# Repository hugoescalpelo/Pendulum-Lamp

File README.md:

# Pendulum Lamp

An Iván Abreu Studio Project

This is a project that keeps a pendulum moving

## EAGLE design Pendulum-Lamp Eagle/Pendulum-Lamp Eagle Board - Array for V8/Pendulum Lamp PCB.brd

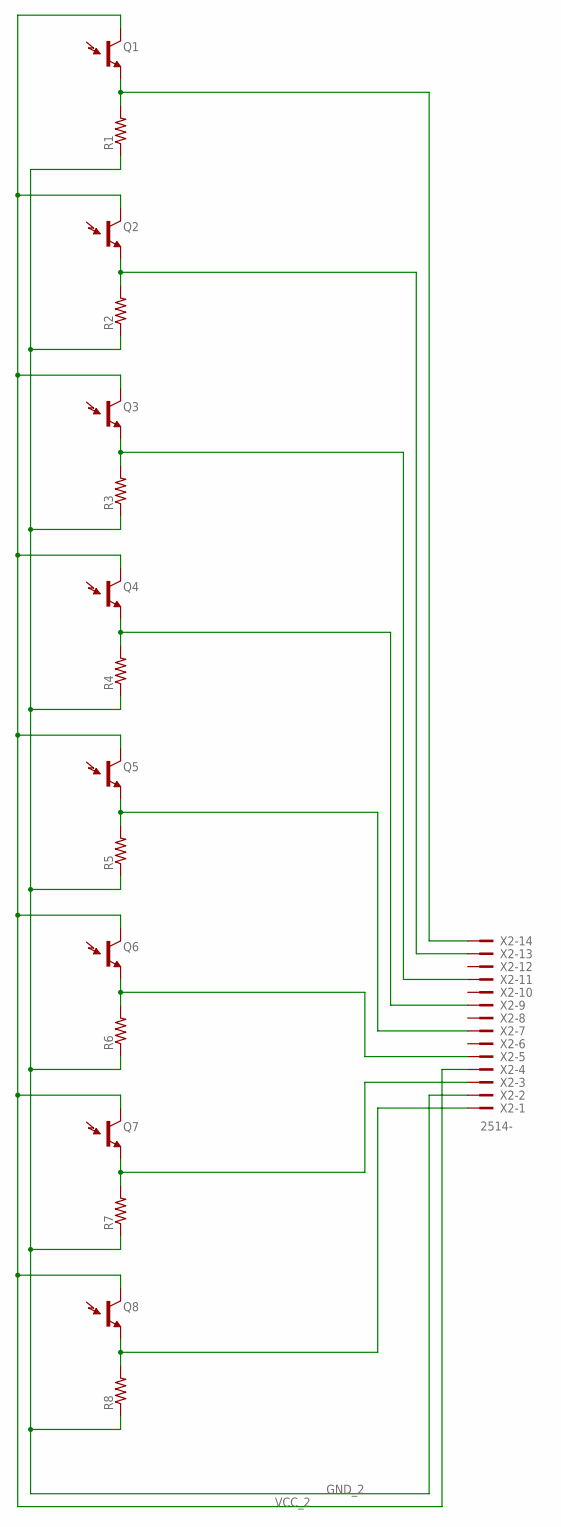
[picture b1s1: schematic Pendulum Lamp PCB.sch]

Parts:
Q1, Q2, Q3, Q4, Q5, Q6, Q7, Q8: LTR-301
R1, R2, R3, R4, R5, R6, R7, R8: R-US_0204/7; 0204/7
X2: 2514-; PAK100/2500-14

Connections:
GND_2: R1.1, R2.1, R3.1, R4.1, R5.1, R6.1, R7.1, R8.1, X2.2
unnamed: Q1.E (E1), R1.2, X2.14
unnamed: Q2.E (E1), R2.2, X2.13
unnamed: Q3.E (E1), R3.2, X2.11
unnamed: Q4.E (E1), R4.2, X2.9
unnamed: Q5.E (E1), R5.2, X2.7
unnamed: Q6.E (E1), R6.2, X2.5
unnamed: Q7.E (E1), R7.2, X2.3
unnamed: Q8.E (E1), R8.2, X2.1
VCC_2: Q1.C (C1), Q2.C (C1), Q3.C (C1), Q4.C (C1), Q5.C (C1), Q6.C (C1), Q7.C (C1), Q8.C (C1), X2.4

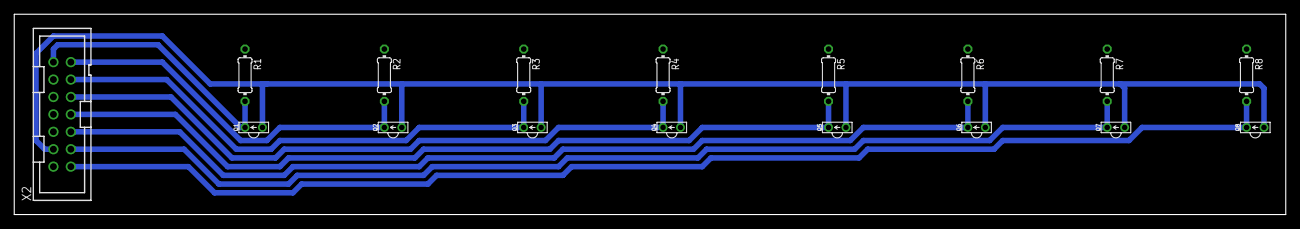
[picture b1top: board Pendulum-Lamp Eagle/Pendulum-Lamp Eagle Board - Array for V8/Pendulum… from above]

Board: 2 copper layers, 185.4 x 29.2 mm, 17 parts (0 on the bottom side), 10 nets.

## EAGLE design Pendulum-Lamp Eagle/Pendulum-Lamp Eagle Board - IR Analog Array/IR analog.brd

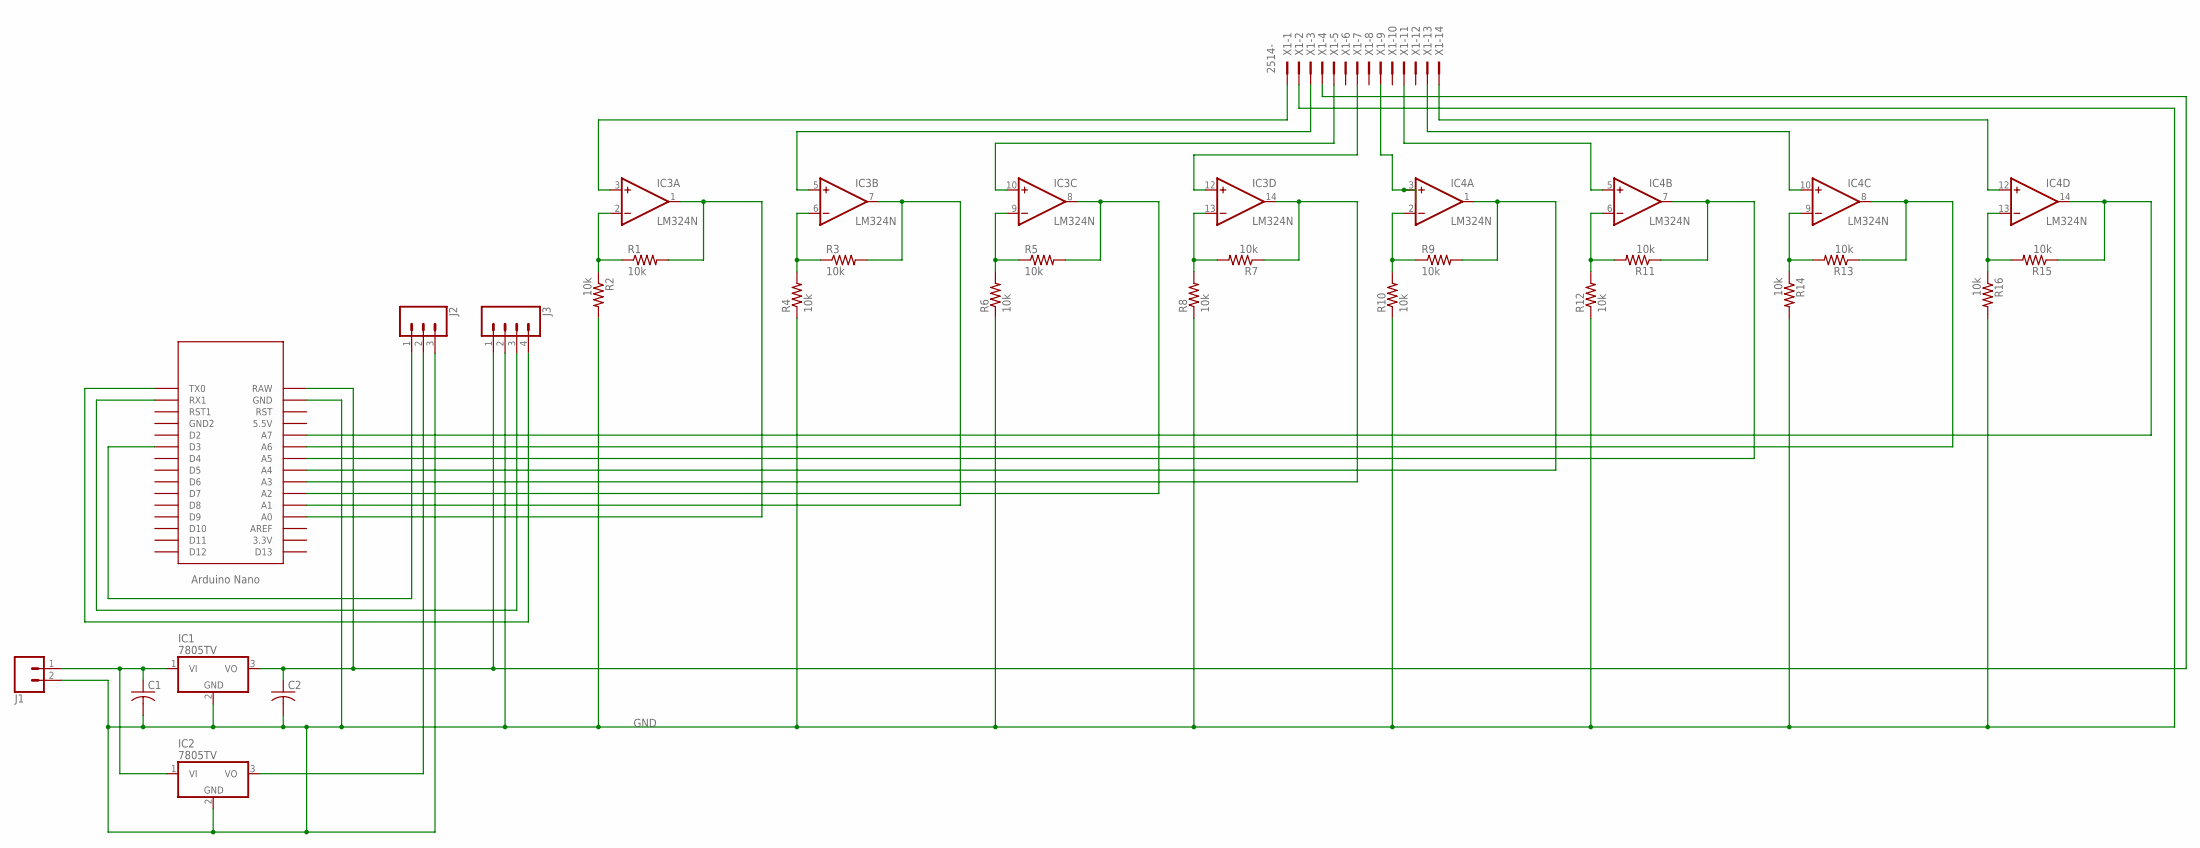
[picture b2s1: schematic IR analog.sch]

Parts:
C1, C2: C-US025-060X050; C025-060X050
IC1, IC2: 7805TV; TO220V
IC3, IC4: LM324N; DIL14
J1: CONN_023.5MM_LOCK; SCREWTERMINAL-3.5MM-2_LOCK
J2: CONN_03LONGPADS; 1X03_LONGPADS
J3: CONN_04LONGPADS; 1X04_LONGPADS
R1, R2, R3, R4, R5, R6, R7, R8, R9, R10, R11, R12, R13, R14, R15, R16: 10k; 0204/5
U$1: NANO
X1: 2514-; PAK100/2500-14

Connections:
GND: C1.2, C2.2, IC1.2 (GND), IC2.2 (GND), IC3.11 (V-), IC4.11 (V-), J1.2, J2.3, J3.2, R2.2, R4.1, R6.1, R8.1, R10.1, R12.1, R14.2, R16.2, U$1.GND, X1.2
unnamed: C1.1, IC1.1 (VI), IC2.1 (VI), J1.1
unnamed: C2.1, IC1.3 (VO), J3.1, U$1.RAW, X1.4
unnamed: IC4.9 (-IN), R13.2, R14.1
unnamed: IC3.2 (-IN), R1.1, R2.1
unnamed: IC3.1 (OUT), R1.2, U$1.A0
unnamed: IC3.7 (OUT), R3.2, U$1.A1
unnamed: IC3.6 (-IN), R3.1, R4.2
unnamed: IC3.8 (OUT), R5.2, U$1.A2
unnamed: IC3.9 (-IN), R5.1, R6.2
unnamed: IC3.13 (-IN), R7.2, R8.2
unnamed: IC3.14 (OUT), R7.1, U$1.A3
unnamed: IC4.1 (OUT), R9.2, U$1.A4
unnamed: IC4.2 (-IN), R9.1, R10.2
unnamed: IC4.6 (-IN), R11.2, R12.2
unnamed: IC4.7 (OUT), R11.1, U$1.A5
unnamed: IC4.8 (OUT), R13.1, U$1.A6
unnamed: IC4.14 (OUT), R15.1, U$1.A7
unnamed: IC4.13 (-IN), R15.2, R16.1
unnamed: IC3.3 (+IN), X1.1
unnamed: IC3.5 (+IN), X1.3
unnamed: IC3.10 (+IN), X1.5
unnamed: IC3.12 (+IN), X1.7
unnamed: IC4.3 (+IN), X1.9
unnamed: IC4.10 (+IN), X1.13
unnamed: IC4.5 (+IN), X1.11
unnamed: IC4.12 (+IN), X1.14
unnamed: J2.1, U$1.D3
unnamed: IC2.3 (VO), J2.2
unnamed: J3.3, U$1.RX1
unnamed: J3.4, U$1.TX0
V+: IC3.4 (V+), IC4.4 (V+)

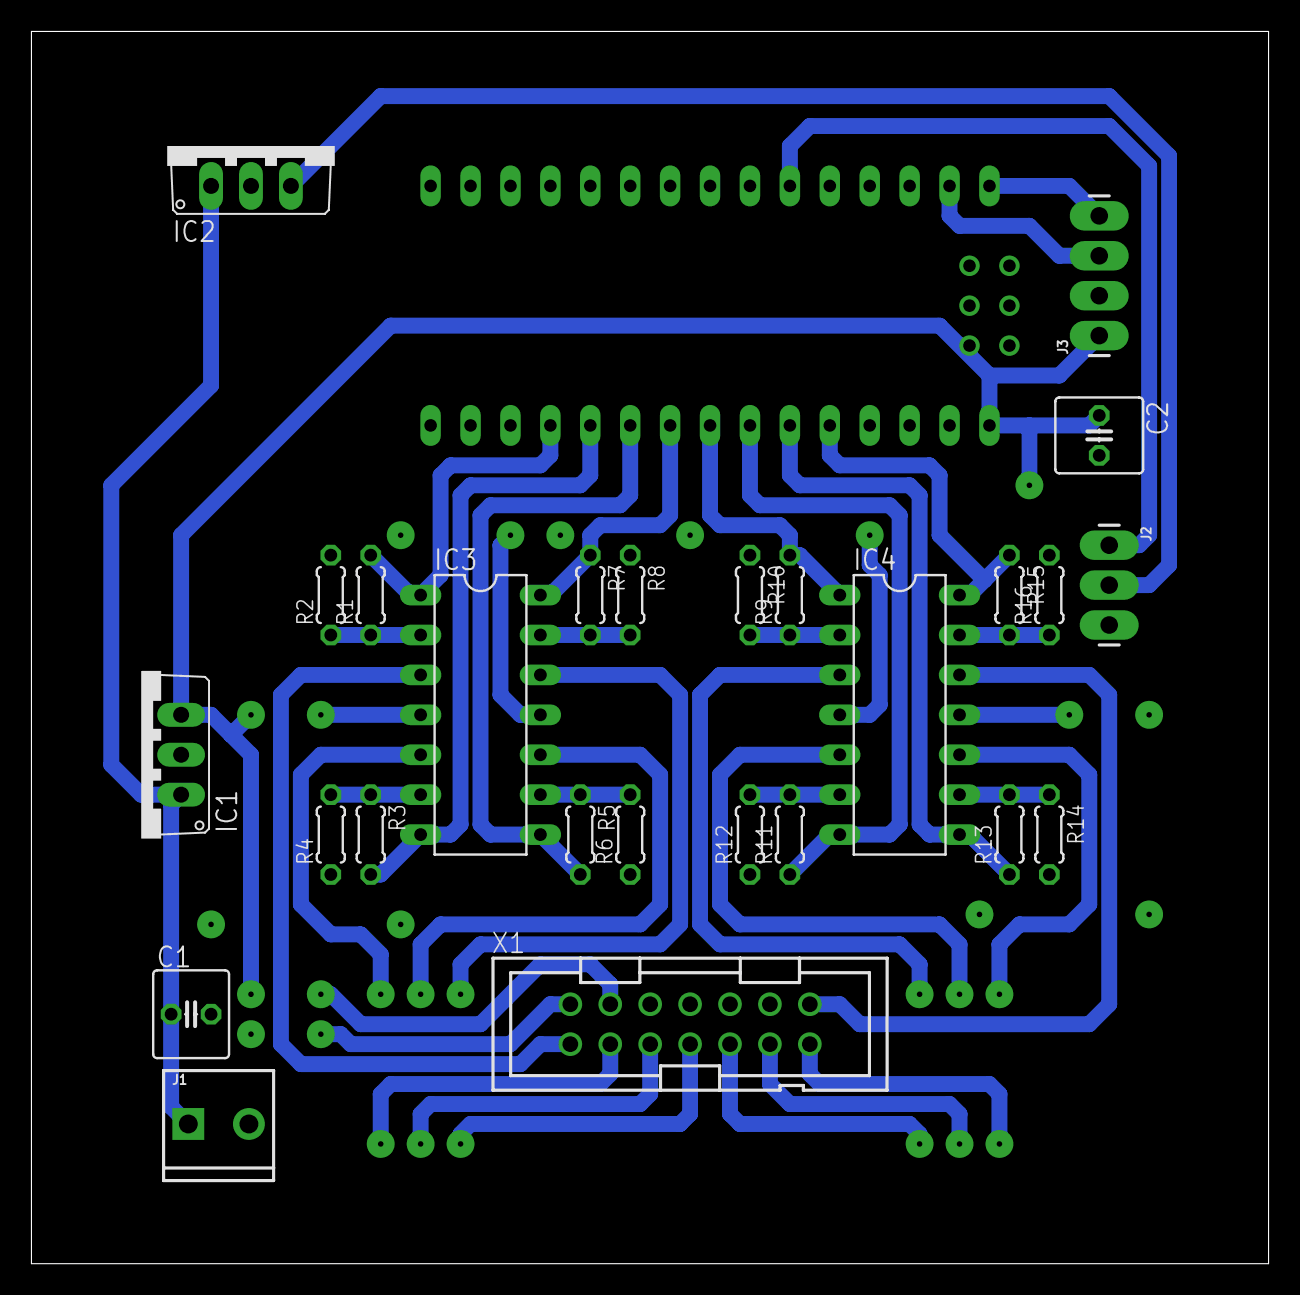
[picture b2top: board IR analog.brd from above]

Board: 2 copper layers, 78.7 x 78.4 mm, 27 parts (0 on the bottom side), 32 nets.

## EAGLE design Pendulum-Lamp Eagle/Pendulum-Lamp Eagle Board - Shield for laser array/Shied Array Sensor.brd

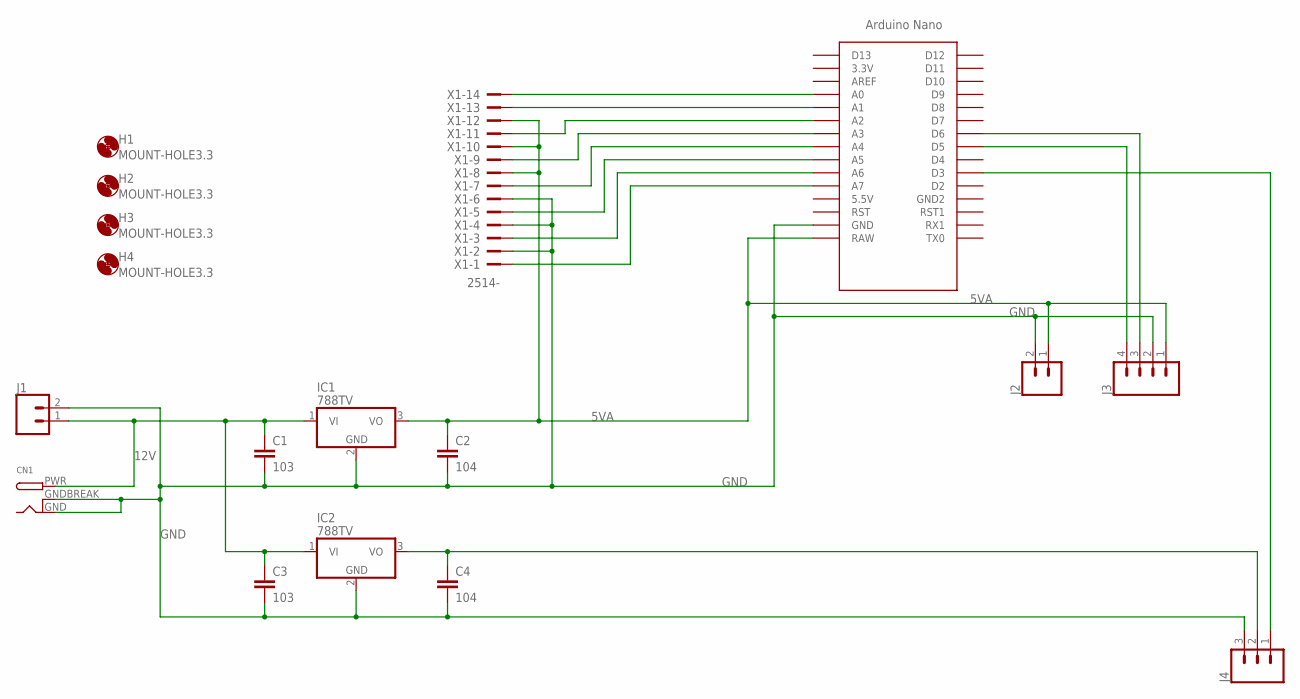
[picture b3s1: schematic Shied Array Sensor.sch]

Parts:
C1, C3: 103; C050-024X044
C2, C4: 104; C050-024X044
CN1: DCBARRELPTH; DCJACK_2MM_PTH
H1, H2, H3, H4: MOUNT-HOLE3.3; 3,3
IC1, IC2: 788TV; TO220V
J1, J2: CONN_023.5MM_LOCK; SCREWTERMINAL-3.5MM-2_LOCK
J3: CONN_04LONGPADS; 1X04_LONGPADS
J4: CONN_03LONGPADS; 1X03_LONGPADS
U$1: NANO
X1: 2514-; PAK100/2500-14

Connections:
5VA: C2.1, IC1.3 (VO), J2.1, J3.1, U$1.RAW, X1.8, X1.10, X1.12
12V: C1.1, C3.1, CN1.PWR, IC1.1 (VI), IC2.1 (VI), J1.1
GND: C1.2, C2.2, C3.2, C4.2, CN1.GND, CN1.GNDBREAK, IC1.2 (GND), IC2.2 (GND), J1.2, J2.2, J3.2, J4.3, U$1.GND, X1.2, X1.4, X1.6
unnamed: U$1.A0, X1.14
unnamed: U$1.A1, X1.13
unnamed: U$1.A2, X1.11
unnamed: U$1.A3, X1.9
unnamed: U$1.A4, X1.7
unnamed: U$1.A5, X1.5
unnamed: U$1.A6, X1.3
unnamed: U$1.A7, X1.1
unnamed: J3.4, U$1.D5
unnamed: C4.1, IC2.3 (VO), J4.2
unnamed: J3.3, U$1.D6
unnamed: J4.1, U$1.D3

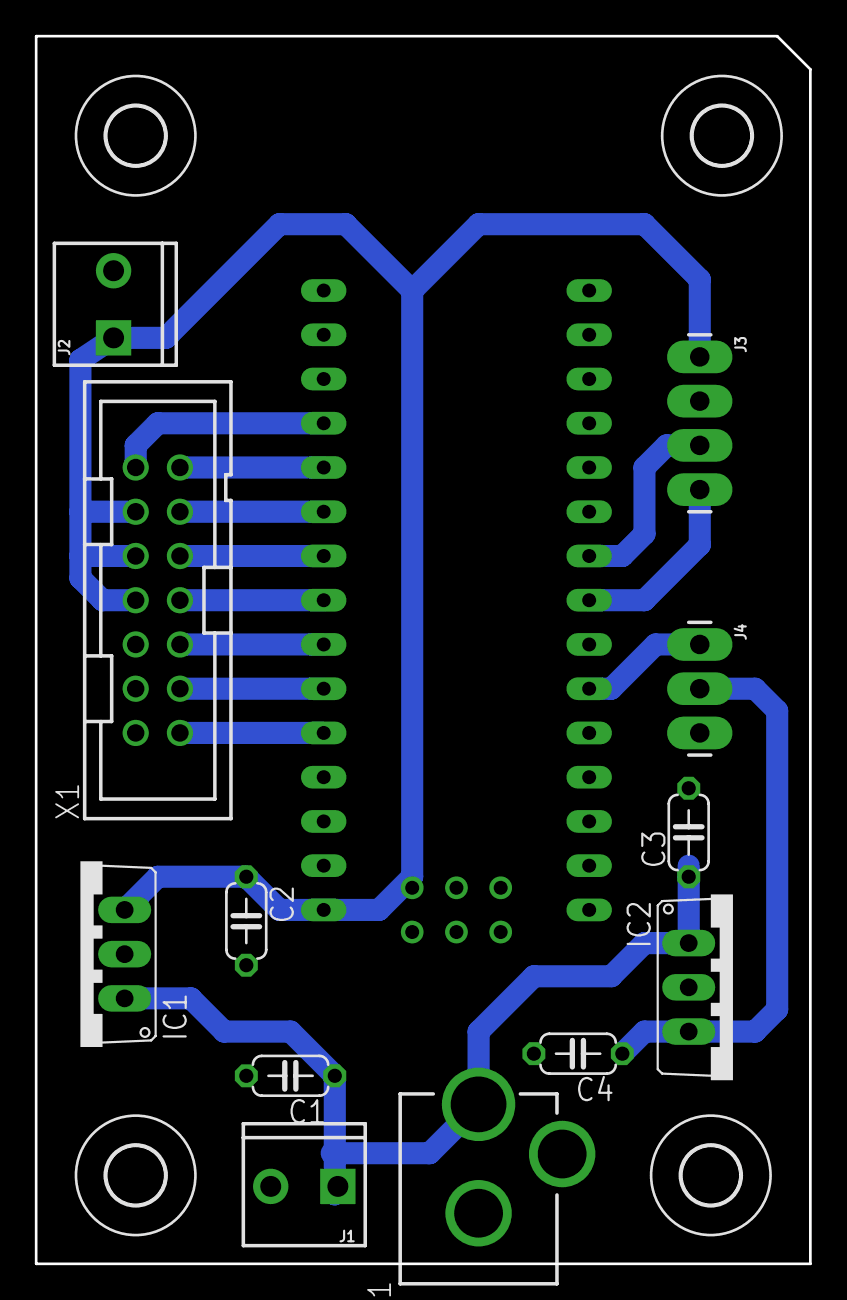
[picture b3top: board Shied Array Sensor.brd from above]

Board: 2 copper layers, 44.4 x 70.5 mm, 17 parts (0 on the bottom side), 15 nets.

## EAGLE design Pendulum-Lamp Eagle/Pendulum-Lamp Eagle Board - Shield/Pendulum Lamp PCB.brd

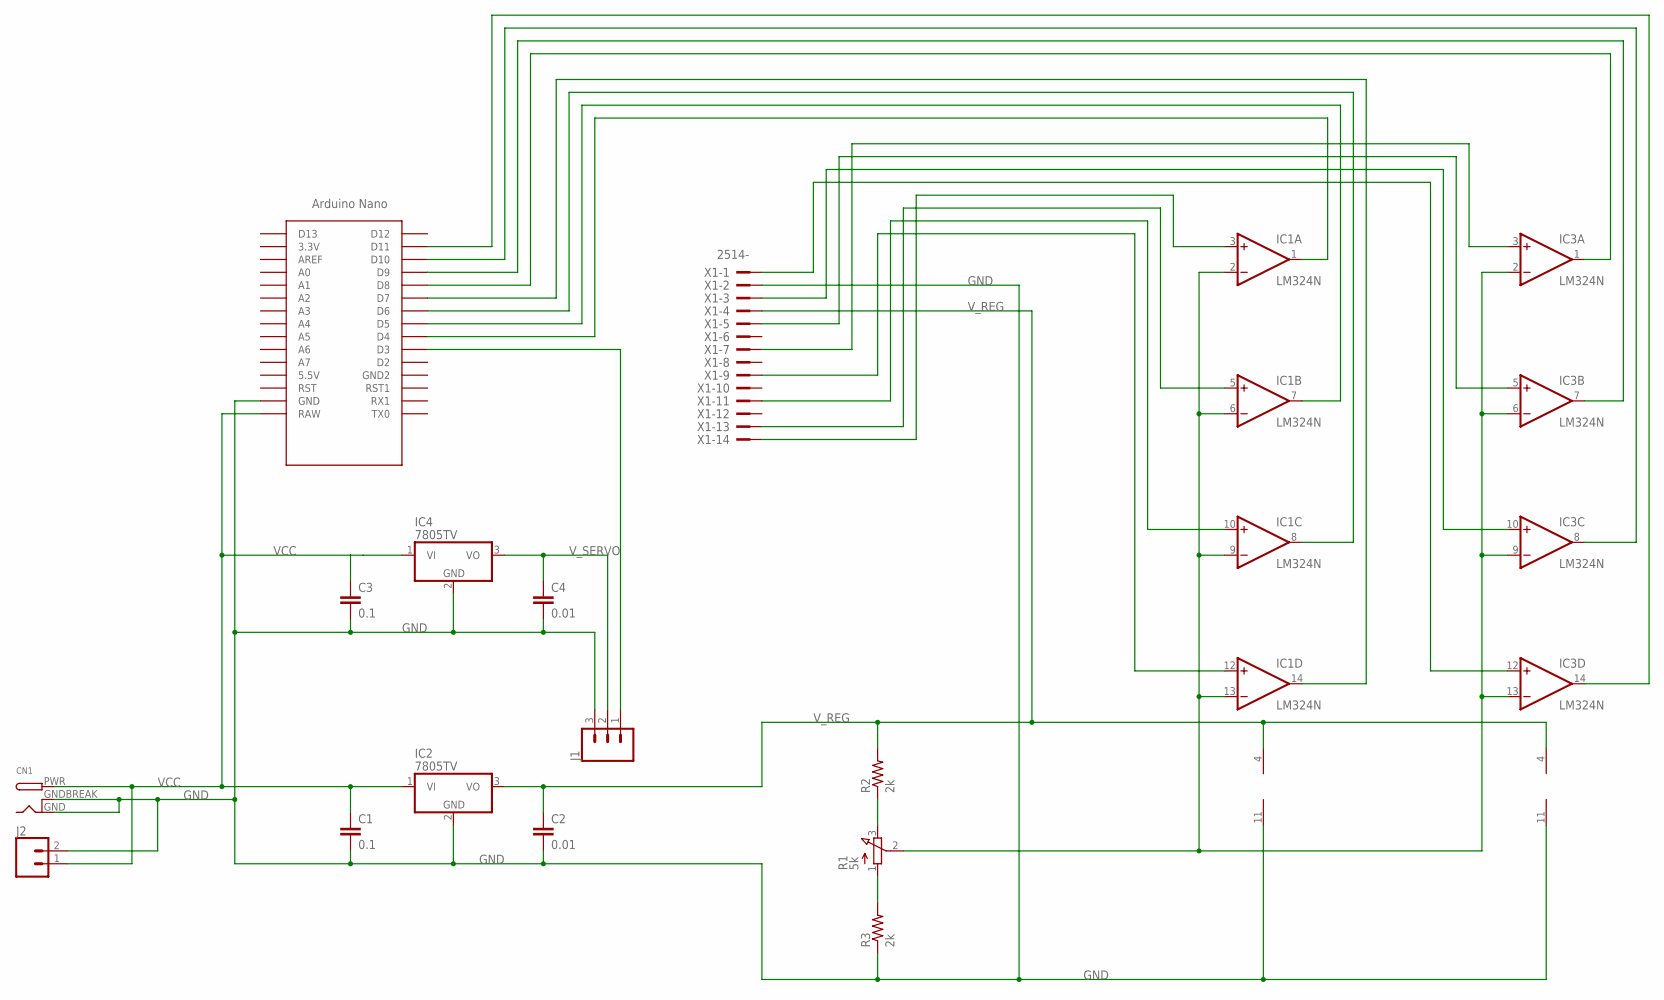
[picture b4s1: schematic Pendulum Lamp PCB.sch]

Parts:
C1, C3: 0.1; C025-030X050
C2, C4: 0.01; C025-030X050
CN1: DCBARRELPTH; DCJACK_2MM_PTH
IC1, IC3: LM324N; DIL14
IC2, IC4: 7805TV; TO220V
J1: CONN_03LONGPADS; 1X03_LONGPADS
J2: CONN_023.5MM_LOCK; SCREWTERMINAL-3.5MM-2_LOCK
R1: 5k; 3RP/1610N
R2, R3: 2k; 0204/7
U$1: NANO
X1: 2514-; PAK100/2500-14

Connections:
GND: C1.2, C2.2, C3.2, C4.2, CN1.GND, CN1.GNDBREAK, IC1.11 (V-), IC2.2 (GND), IC3.11 (V-), IC4.2 (GND), J1.3, J2.2, R3.1, U$1.GND, X1.2
unnamed: IC1.3 (+IN), X1.14
unnamed: IC3.5 (+IN), X1.5
unnamed: J1.1, U$1.D3
unnamed: IC3.10 (+IN), X1.3
unnamed: R1.1 (A), R3.2
unnamed: R1.3 (E), R2.1
unnamed: IC1.2 (-IN), IC1.6 (-IN), IC1.9 (-IN), IC1.13 (-IN), IC3.2 (-IN), IC3.6 (-IN), IC3.9 (-IN), IC3.13 (-IN), R1.2 (S)
unnamed: IC1.1 (OUT), U$1.D4
unnamed: IC1.7 (OUT), U$1.D5
unnamed: IC1.8 (OUT), U$1.D6
unnamed: IC1.14 (OUT), U$1.D7
unnamed: IC3.1 (OUT), U$1.D8
unnamed: IC3.7 (OUT), U$1.D9
unnamed: IC3.8 (OUT), U$1.D10
unnamed: IC3.14 (OUT), U$1.D11
unnamed: IC3.12 (+IN), X1.1
unnamed: IC1.12 (+IN), X1.9
unnamed: IC1.5 (+IN), X1.13
unnamed: IC1.10 (+IN), X1.11
unnamed: IC3.3 (+IN), X1.7
VCC: C1.1, C3.1, CN1.PWR, IC2.1 (VI), IC4.1 (VI), J2.1, U$1.RAW
V_REG: C2.1, IC1.4 (V+), IC2.3 (VO), IC3.4 (V+), R2.2, X1.4
V_SERVO: C4.1, IC4.3 (VO), J1.2

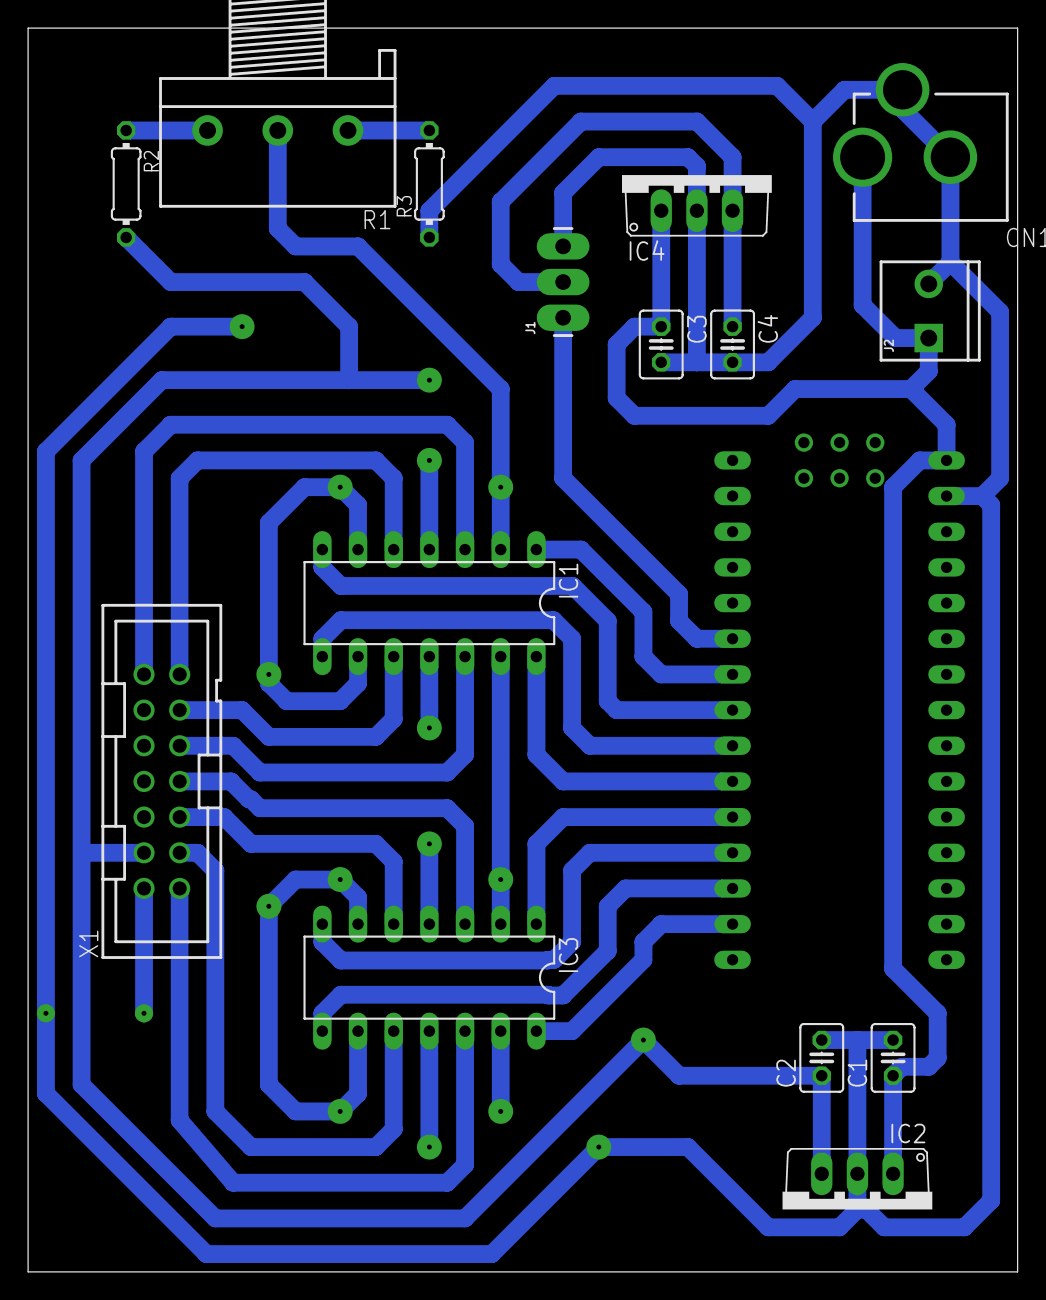
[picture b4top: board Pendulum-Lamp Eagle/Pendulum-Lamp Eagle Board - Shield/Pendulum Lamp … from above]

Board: 2 copper layers, 70.5 x 88.6 mm, 16 parts (0 on the bottom side), 24 nets.

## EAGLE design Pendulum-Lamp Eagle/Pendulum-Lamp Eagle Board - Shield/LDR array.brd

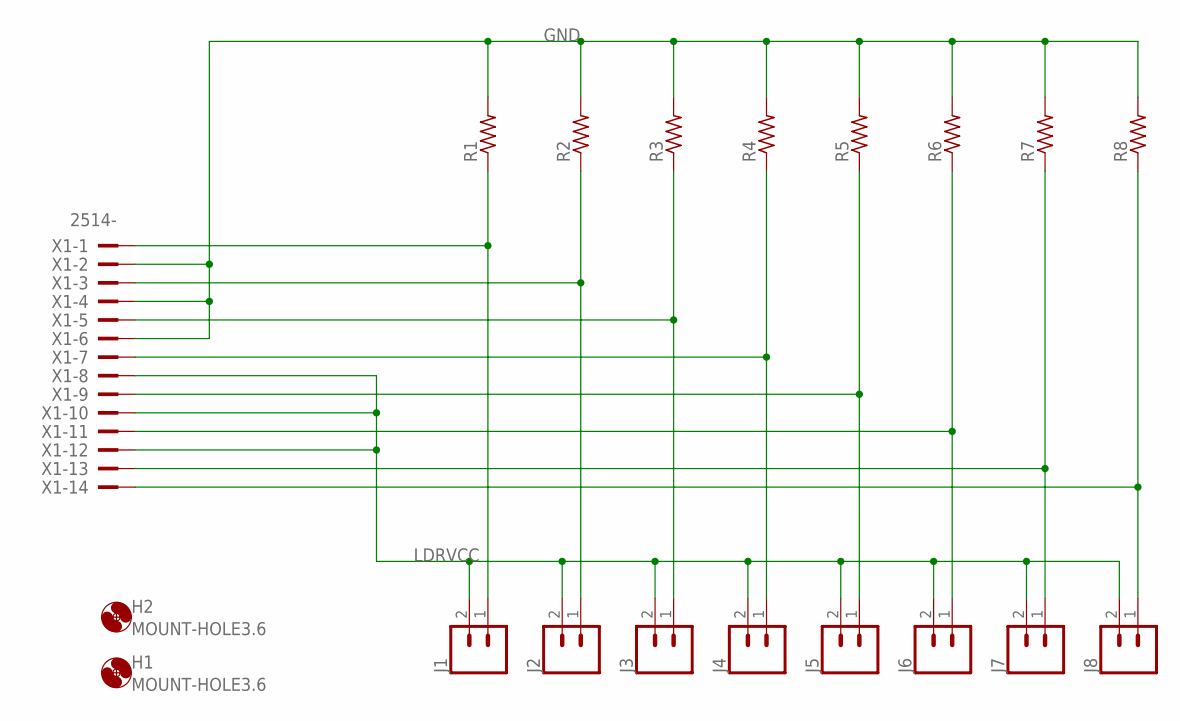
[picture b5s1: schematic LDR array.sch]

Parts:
H1, H2: MOUNT-HOLE3.6; 3,6
J1, J2, J3, J4, J5, J6, J7, J8: CONN_023.5MM_LOCK; SCREWTERMINAL-3.5MM-2_LOCK
R1, R2, R3, R4, R5, R6, R7, R8: R-US_0204/7; 0204/7
X1: 2514-; PAK100/2500-14

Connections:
GND: R1.2, R2.2, R3.2, R4.2, R5.2, R6.2, R7.2, R8.2, X1.2, X1.4, X1.6
LDRVCC: J1.2, J2.2, J3.2, J4.2, J5.2, J6.2, J7.2, J8.2, X1.8, X1.10, X1.12
unnamed: J1.1, R1.1, X1.1
unnamed: J2.1, R2.1, X1.3
unnamed: J3.1, R3.1, X1.5
unnamed: J4.1, R4.1, X1.7
unnamed: J5.1, R5.1, X1.9
unnamed: J6.1, R6.1, X1.11
unnamed: J7.1, R7.1, X1.13
unnamed: J8.1, R8.1, X1.14

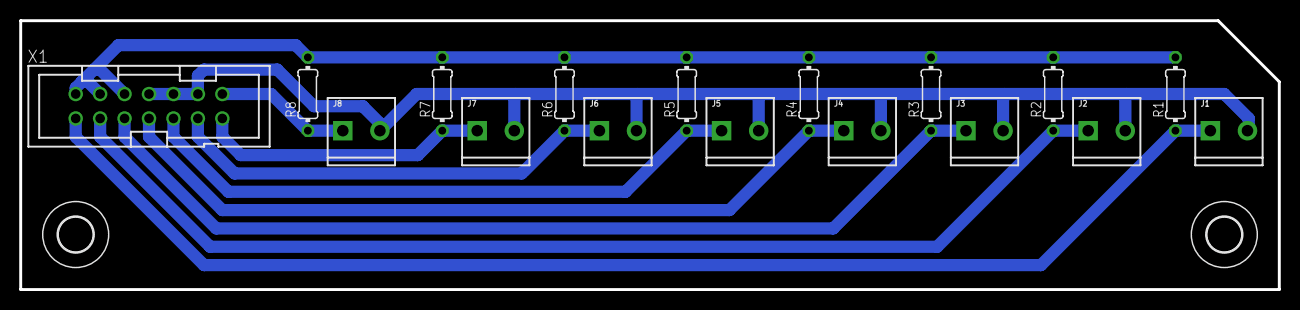
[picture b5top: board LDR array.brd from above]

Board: 2 copper layers, 130.8 x 27.9 mm, 19 parts (0 on the bottom side), 10 nets.

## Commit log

2018-02-13 First files added
2018-02-13 Commentary on Read me file
2018-02-13 Firs commit
    Schematic Added
2018-02-13 Some mechanical references modified
    Re opened assembly files, re adjusts paths to referenced assemby. Made a layout to determine the pcb form factor based on the mechanism. Gosh, maybe I shoud migrate to Fusion 360
2018-02-14 PCB board finished
    Main pcb board finished. Some solid works parts modied
2018-02-14 DXF cam layout added
2018-02-14 CAM DXF file finished
    Added some corrections to schematic supply. DXF file processed.
2018-02-14 Sensor Array finished
    Added sensor array in Eagle and DXF
2018-02-15 CAM Files added
2018-02-19 Test code
    Sensor array test coded completed
2018-02-19 Eagle PCB Project Splitted
2018-02-19 Circuit Holder added
    A 3d printed pieces to make shure the lamp wire stays in IR range
2018-02-20 Circuit Holder splitted
    Circuit holder splitted to 3d printing easyness
2018-02-20 G Code added
2018-02-20 Bitwise operations added
    Arduino code updated with bitwise operations
2018-02-20 First active test working
    A pen has used to obstuct the lamp module and it reacts to the simulating moving of the lamp wire
2018-02-21 Firtst succesful test
    Auto sync achieved. Some minor bugs founded. Stills sync after lose track of the lamps wire position
2018-02-21 Take me out sequence added
    It was needed a take me out sequence because sometimes the lamp get stucked. Also, I need to redesign the way changes are detected
2018-02-21 Updated lecture logics
    The way is read and updated de register info of the sensors reading was corrected. A take me out sequence is not needed anymore, however remains commented.
2018-02-23 Working Code
2018-02-23 Proporcionality at extension and delay time added
2018-02-23 Proportional ignition added
2018-02-24 Test code added
2018-02-24 A little order to the code
    It was a mess
2018-02-27 Laser sensor array started
2018-02-27 Succesful model
    It was needed an alignment in base extensors
2018-02-28 First succesful model
2018-02-28 Circuit adjusted. Laser array sch started
2018-02-28 Laser array and ldr array pcb circuits designed
2018-02-28 Shield pcb first version
2018-02-28 Rhino patter added
2018-03-01 Patern fixed
    Layer ortederd
2018-03-06 New arduino code version
2018-03-06 Working basic laser array fix
2018-03-06 Add promedier function Added
2018-03-06 Primedier trimmer added
2018-03-06 No detect promediator added
2018-03-06 Some order
2018-03-07 New logic code added
2018-03-08 Average sequence added with fixed logics
2018-03-08 Ignition motion detection redesigned
2018-03-09 Servo movement bonded to intensity
2018-03-09 Direction detecto added
2018-03-09 change direction detector with half steps added
2018-03-10 New Logics
2018-03-12 Adjusted to day values
2018-03-12 Adder added
2018-03-12 Dinamic threshold added
2018-03-13 Average sequence added
2018-03-13 lecture feedback
2018-03-13 Self referenced averaged feedback functional version
2018-03-13 Comentary added
2018-03-13 More comentary
2018-03-22 Line laser parts added
2018-05-18 New parts added
2018-06-25 New Design
2018-07-24 Minor changes in arms
    Arms didnt work
2018-07-26 Drawings Added
2018-08-02 WTF
    I don't know what happend here
2018-08-02 Last one change
    from de 61 change

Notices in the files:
parts and their libraries:
SparkFun-Sensors: Licensing: Creative Commons ShareAlike 4.0 International - https://creativecommons.org/licenses/by-sa/4.0
